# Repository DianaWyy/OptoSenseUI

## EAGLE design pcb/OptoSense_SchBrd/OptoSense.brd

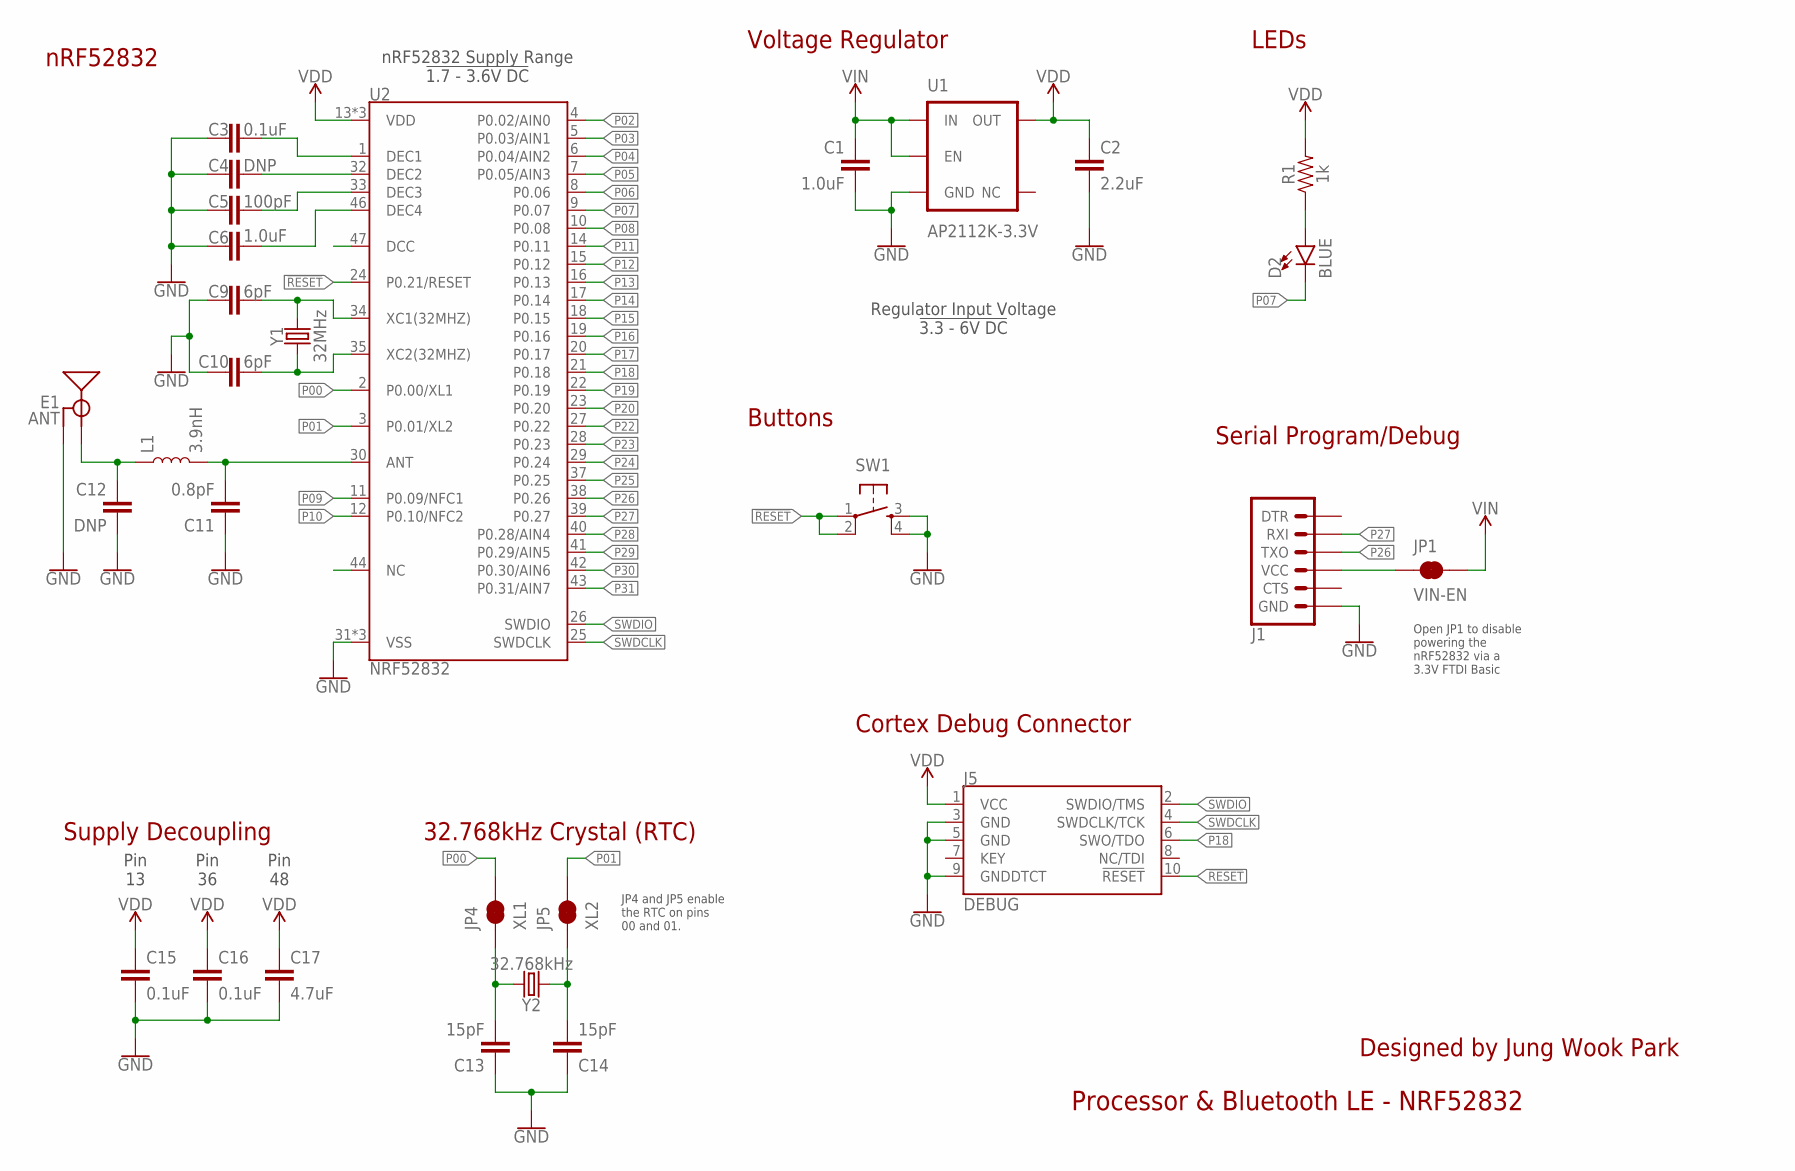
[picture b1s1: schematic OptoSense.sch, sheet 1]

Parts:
C1: 1.0uF; 0603
C2: 2.2uF; 0603
C3, C15, C16: 0.1uF; 0402
C4, C12: DNP; 0402
C5: 100pF; 0402
C6: 1.0uF; 0402
C9, C10: 6pF; 0402
C11: 0.8pF; 0402
C13, C14: 15pF; 0402
C17: 4.7uF; 0603
D2: BLUE; LED-0603
E1: ANT; TRACE_ANTENNA_2.4GHZ_15.2MM
J1: ARDUINO_SERIAL_PROGRAMPTH; 1X06
J5: DEBUG; 2X5-PTH-1.27MM
JP1: VIN-EN; SMT-JUMPER_2_NC_TRACE_SILK
JP4: XL1; PAD-JUMPER-2-NC_BY_TRACE_YES_SILK
JP5: XL2; PAD-JUMPER-2-NC_BY_TRACE_YES_SILK
L1: 3.9nH; 0402
R1: 1k; 0603
SW1: SWITCH_SPST_4_PINRECT; TACTILE_SWITCH_SMD_4.6X2.8MM
U1: AP2112K-3.3V; SOT23-5
U2: NRF52832; QFN48-6X6MM
Y1: 32MHz; CRYSTAL-SMD-2.0X1.6MM
Y2: 32.768kHz; CRYSTAL-SMD-3.2X1.5MM

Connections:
!RESET!: J5.10 (!RESET), SW1.1, SW1.2, U2.24 (P0.21/RESET)
ANT: C11.2, L1.2, U2.30 (ANT)
DCC: U2.47 (DCC)
DEC1: C3.2, U2.1 (DEC1)
DEC2: C4.2, U2.32 (DEC2)
DEC3: C5.2, U2.33 (DEC3)
DEC4: C6.2, U2.46 (DEC4)
GND: C1.2, C2.2, C3.1, C4.1, C5.1, C6.1, C9.1, C10.2, C11.1, C12.2, C13.1, C14.1, C15.2, C16.2, C17.2, E1.GND, J1.6 (GND), J5.3 (GND), J5.5 (GND), J5.9 (GNDDTCT), SW1.3, SW1.4, U1.2 (GND), U2.31 (VSS), U2.45 (VSS), U2.EP (VSS); also elsewhere on the board
unnamed: C13.2, JP4.1, Y2.P$2 (2)
unnamed: C14.2, JP5.1, Y2.P$1 (1)
unnamed: C12.1, E1.ANT (SIGNAL), L1.1
unnamed: J1.4 (VCC), JP1.1
unnamed: D2.A, R1.1
NC: U2.44 (NC)
P00: JP4.2, U2.2 (P0.00/XL1)
P01: JP5.2, U2.3 (P0.01/XL2)
P02: U2.4 (P0.02/AIN0); also elsewhere on the board
P03: U2.5 (P0.03/AIN1); also elsewhere on the board
P04: U2.6 (P0.04/AIN2); also elsewhere on the board
P05: U2.7 (P0.05/AIN3); also elsewhere on the board
P06: U2.8 (P0.06)
P07: D2.C, U2.9 (P0.07)
P08: U2.10 (P0.08)
P09: U2.11 (P0.09/NFC1)
P10: U2.12 (P0.10/NFC2)
P11: U2.14 (P0.11)
P12: U2.15 (P0.12)
P13: U2.16 (P0.13)
P14: U2.17 (P0.14)
P15: U2.18 (P0.15)
P16: U2.19 (P0.16)
P17: U2.20 (P0.17)
P18: J5.6 (SWO/TDO), U2.21 (P0.18)
P19: U2.22 (P0.19)
P20: U2.23 (P0.20)
P22: U2.27 (P0.22); also elsewhere on the board
P23: U2.28 (P0.23); also elsewhere on the board
P24: U2.29 (P0.24); also elsewhere on the board
P25: U2.37 (P0.25); also elsewhere on the board
P26: J1.3 (TXO), U2.38 (P0.26)
P27: J1.2 (RXI), U2.39 (P0.27)
P28: U2.40 (P0.28/AIN4); also elsewhere on the board
P29: U2.41 (P0.29/AIN5); also elsewhere on the board
P30: U2.42 (P0.30/AIN6); also elsewhere on the board
P31: U2.43 (P0.31/AIN7); also elsewhere on the board
SWDCLK: J5.4 (SWDCLK/TCK), U2.25 (SWDCLK)
SWDIO: J5.2 (SWDIO/TMS), U2.26 (SWDIO)
VDD: C2.1, C15.1, C16.1, C17.1, J5.1 (VCC), R1.2, U1.5 (OUT), U2.13 (VDD), U2.36 (VDD), U2.48 (VDD); also elsewhere on the board
VIN: C1.1, JP1.2, U1.1 (IN), U1.3 (EN); also elsewhere on the board
XC1: C9.2, U2.34 (XC1(32MHZ)), Y1.3 (2)
XC2: C10.1, U2.35 (XC2(32MHZ)), Y1.1

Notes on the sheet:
Pin 13
Pin 36
Pin 48
Voltage Regulator
Buttons
LEDs
nRF52832
32.768kHz Crystal (RTC)
Supply Decoupling
Cortex Debug Connector
Serial Program/Debug
Open JP1 to disable powering the nRF52832 via a 3.3V FTDI Basic
JP4 and JP5 enable the RTC on pins 00 and 01.
Regulator Input Voltage !3.3 - 6V DC!
nRF52832 Supply Range !1.7 - 3.6V DC!
Processor & Bluetooth LE - NRF52832
Designed by Jung Wook Park

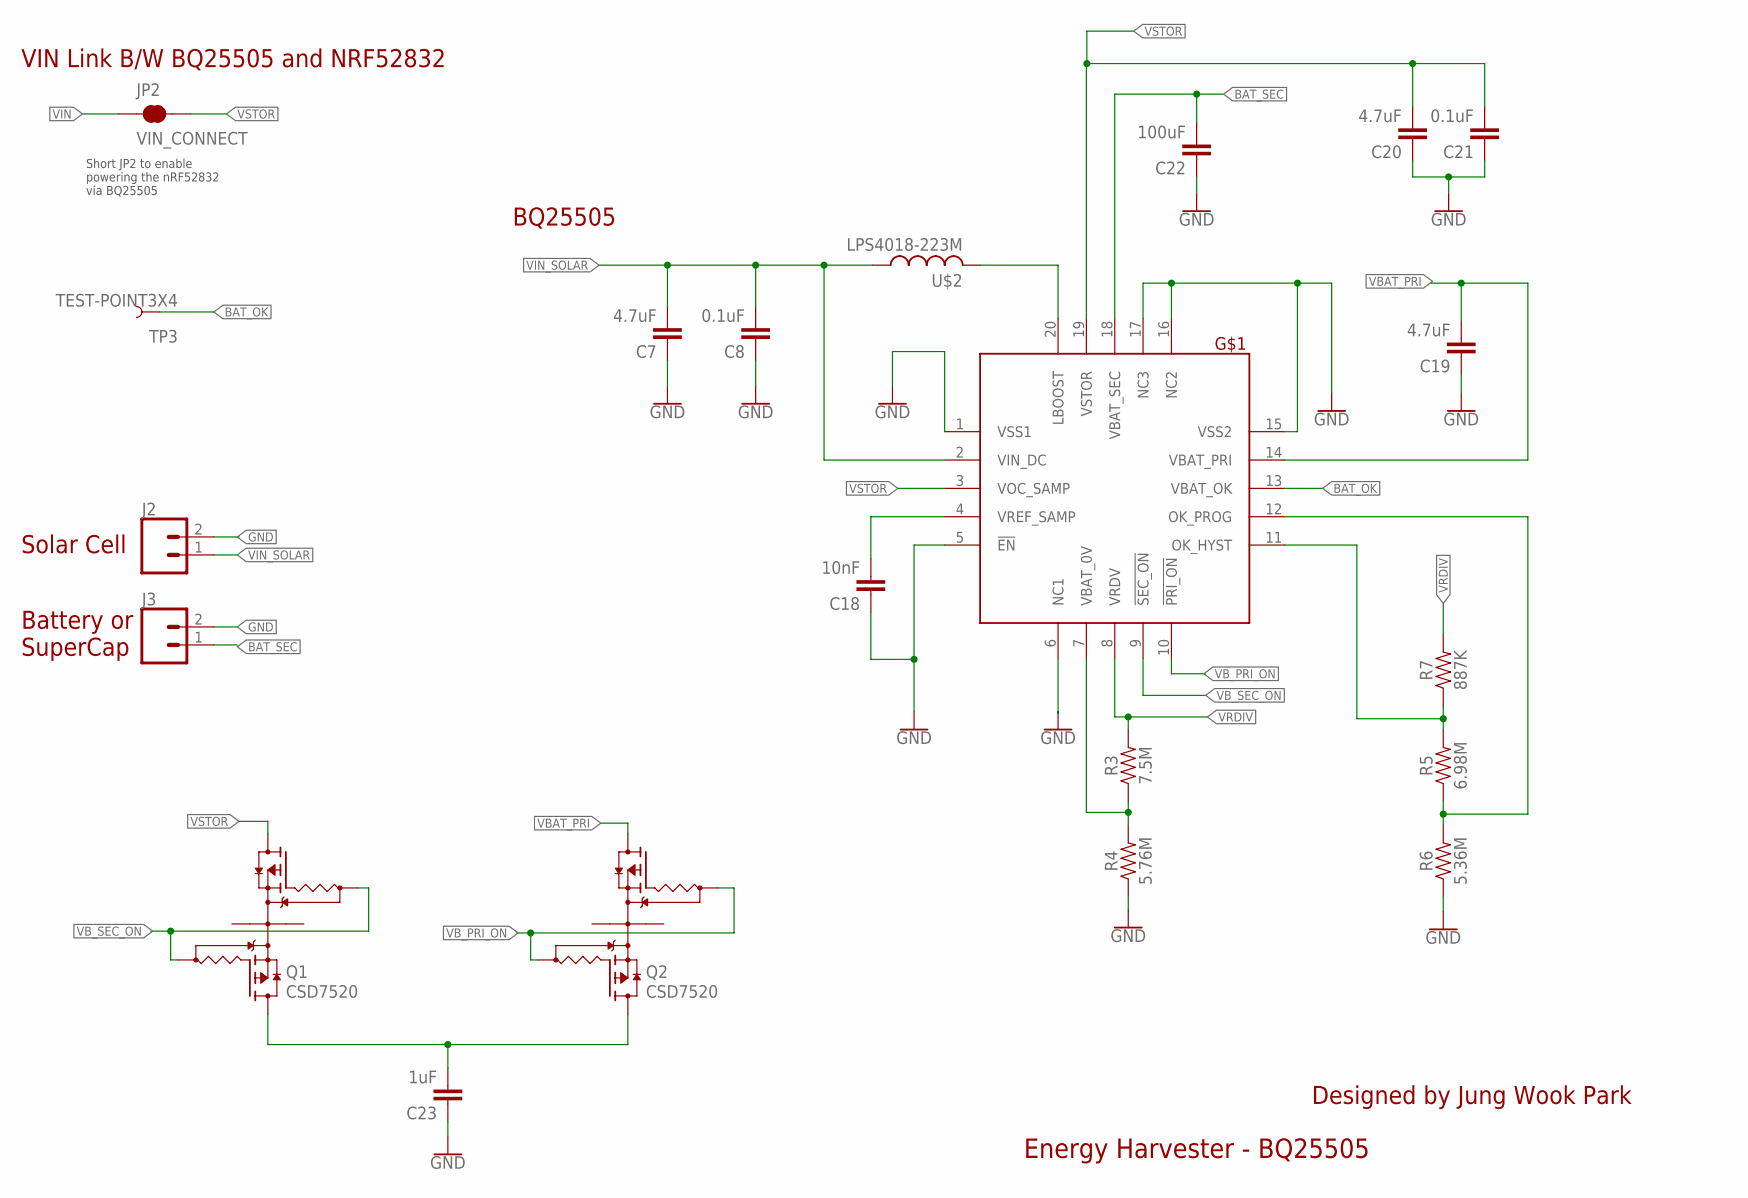
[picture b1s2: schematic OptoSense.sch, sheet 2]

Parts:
C7, C19, C20: 4.7uF; 0402
C8, C21: 0.1uF; 0402
C18: 10nF; 0402
C22: 100uF; 0402
C23: 1uF; 0402
J2, J3: CONN_02; 1X02
JP2: VIN_CONNECT; SMT-JUMPER_2_NC_TRACE_SILK
Q1, Q2: CSD7520; CSD75205W1015
R3: 7.5M; 0603
R4: 5.76M; 0603
R5: 6.98M; 0603
R6: 5.36M; 0603
R7: 887K; 0603
TP3: TEST-POINT3X4; PAD.03X.04
U$1: BQ25505; QFN20
U$2: LPS4018-223M; LPS4018

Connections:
BAT_OK: TP3.P$1, U$1.13 (VBAT_OK)
BAT_SEC: C22.2, J3.1, U$1.18 (VBAT_SEC)
GND: C7.1, C8.1, C18.1, C19.1, C20.1, C21.1, C22.1, C23.1, J2.2, J3.2, R4.1, R6.1, U$1.1 (VSS1), U$1.5 (!EN), U$1.6 (NC1), U$1.15 (VSS2), U$1.16 (NC2), U$1.17 (NC3); also elsewhere on the board
unnamed: U$1.20 (LBOOST), U$2.P$2 (2)
unnamed: C18.2, U$1.4 (VREF_SAMP)
unnamed: R3.1, R4.2, U$1.7 (VBAT_0V)
unnamed: R5.1, R6.2, U$1.12 (OK_PROG)
unnamed: R5.2, R7.1, U$1.11 (OK_HYST)
unnamed: C23.2, Q1.D1, Q2.D1
VBAT_PRI: C19.2, Q2.D2, U$1.14 (VBAT_PRI)
VB_PRI_ON: Q2.G1, Q2.G2, U$1.10 (!PRI_ON)
VB_SEC_ON: Q1.G1, Q1.G2, U$1.9 (!SEC_ON)
VIN: JP2.1; also elsewhere on the board
VIN_SOLAR: C7.2, C8.2, J2.1, U$1.2 (VIN_DC), U$2.P$1 (1)
VRDIV: R3.2, R7.2, U$1.8 (VRDV)
VSTOR: C20.2, C21.2, JP2.2, Q1.D2, U$1.3 (VOC_SAMP), U$1.19 (VSTOR)

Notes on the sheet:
Energy Harvester - BQ25505
BQ25505
Solar Cell
Battery or SuperCap
Short JP2 to enable powering the nRF52832 via BQ25505
VIN Link B/W BQ25505 and NRF52832
Designed by Jung Wook Park

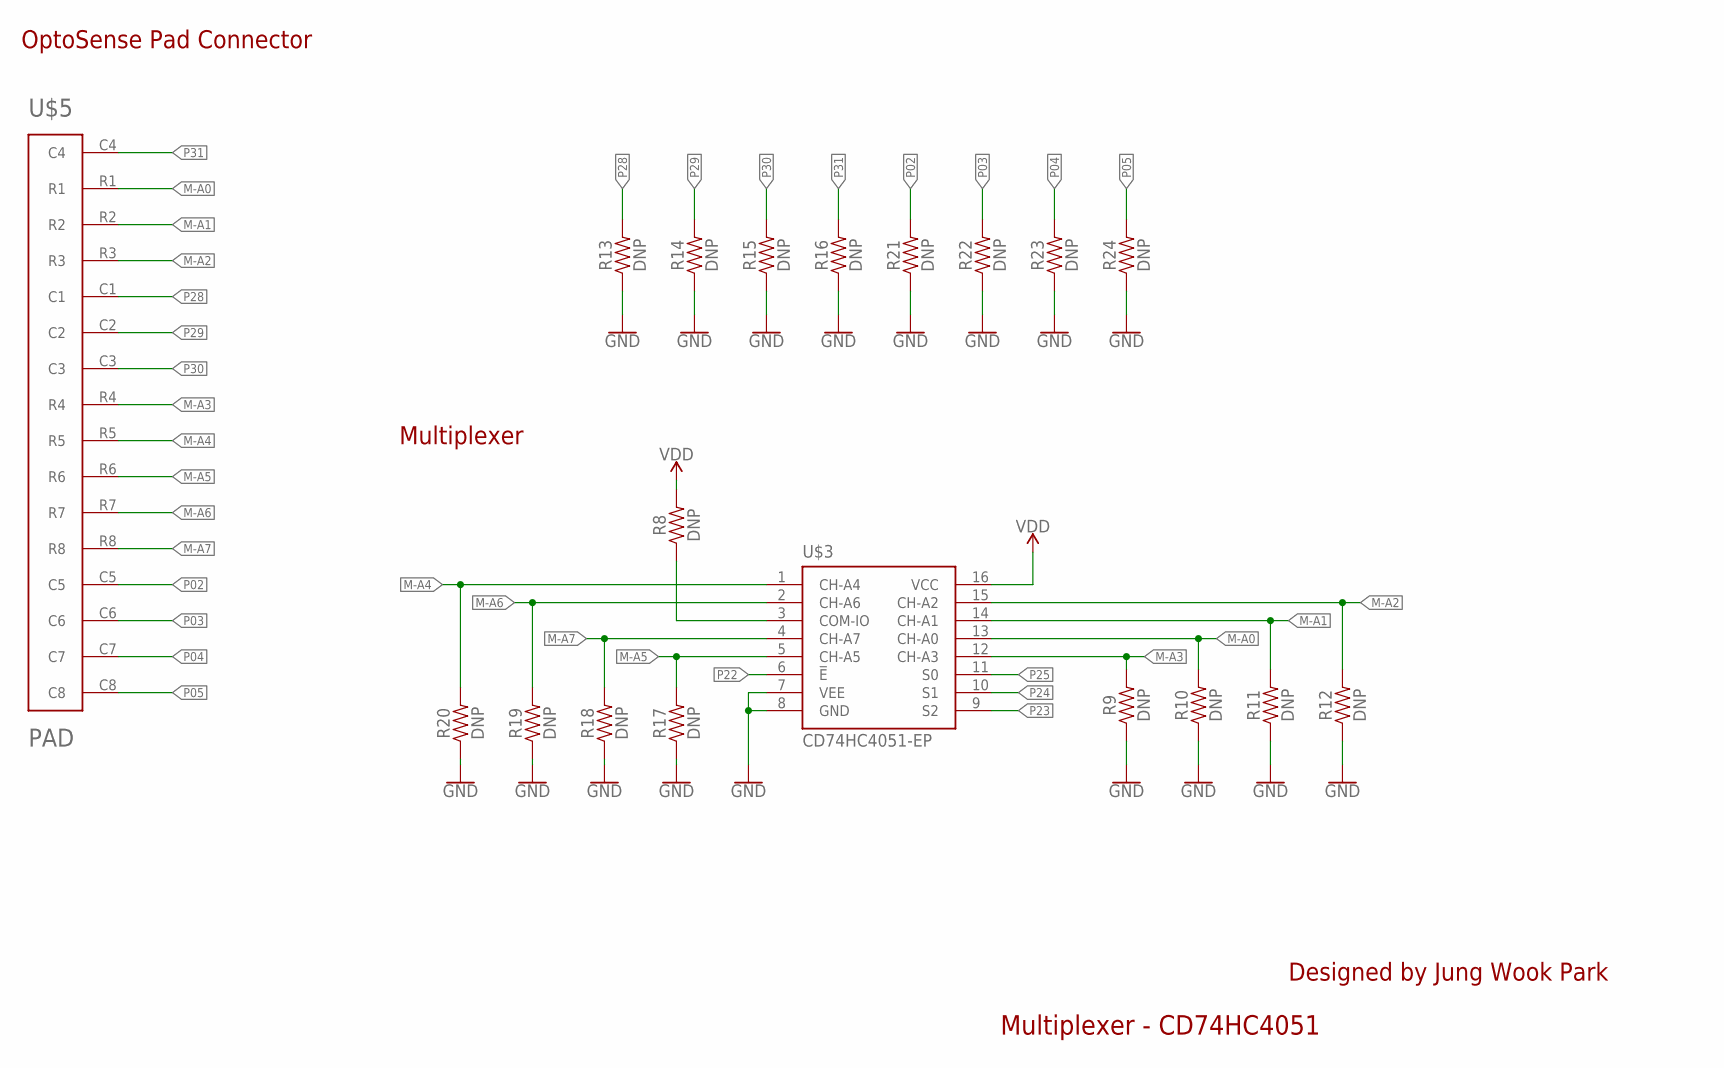
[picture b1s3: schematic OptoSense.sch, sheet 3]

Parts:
R8, R9, R10, R11, R12, R13, R14, R15, R16, R17, R18, R19, R20, R21, R22, R23, R24: DNP; 0603
U$3: CD74HC4051-EP; SO16
U$5: PAD; PADS-16

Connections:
GND: R9.1, R10.1, R11.1, R12.1, R13.1, R14.1, R15.1, R16.1, R17.1, R18.1, R19.1, R20.1, R21.1, R22.1, R23.1, R24.1, U$3.7 (VEE), U$3.8 (GND); also elsewhere on the board
M-A0: R10.2, U$3.13 (CH-A0), U$5.R1
M-A1: R11.2, U$3.14 (CH-A1), U$5.R2
M-A2: R12.2, U$3.15 (CH-A2), U$5.R3
M-A3: R9.2, U$3.12 (CH-A3), U$5.R4
M-A4: R20.2, U$3.1 (CH-A4), U$5.R5
M-A5: R17.2, U$3.5 (CH-A5), U$5.R6
M-A6: R19.2, U$3.2 (CH-A6), U$5.R7
M-A7: R18.2, U$3.4 (CH-A7), U$5.R8
unnamed: R8.1, U$3.3 (COM-IO)
P02: R21.2, U$5.C5; also elsewhere on the board
P03: R22.2, U$5.C6; also elsewhere on the board
P04: R23.2, U$5.C7; also elsewhere on the board
P05: R24.2, U$5.C8; also elsewhere on the board
P22: U$3.6 (!E); also elsewhere on the board
P23: U$3.9 (S2); also elsewhere on the board
P24: U$3.10 (S1); also elsewhere on the board
P25: U$3.11 (S0); also elsewhere on the board
P28: R13.2, U$5.C1; also elsewhere on the board
P29: R14.2, U$5.C2; also elsewhere on the board
P30: R15.2, U$5.C3; also elsewhere on the board
P31: R16.2, U$5.C4; also elsewhere on the board
VDD: R8.2, U$3.16 (VCC); also elsewhere on the board

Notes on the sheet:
Designed by Jung Wook Park
Multiplexer - CD74HC4051
Multiplexer
OptoSense Pad Connector

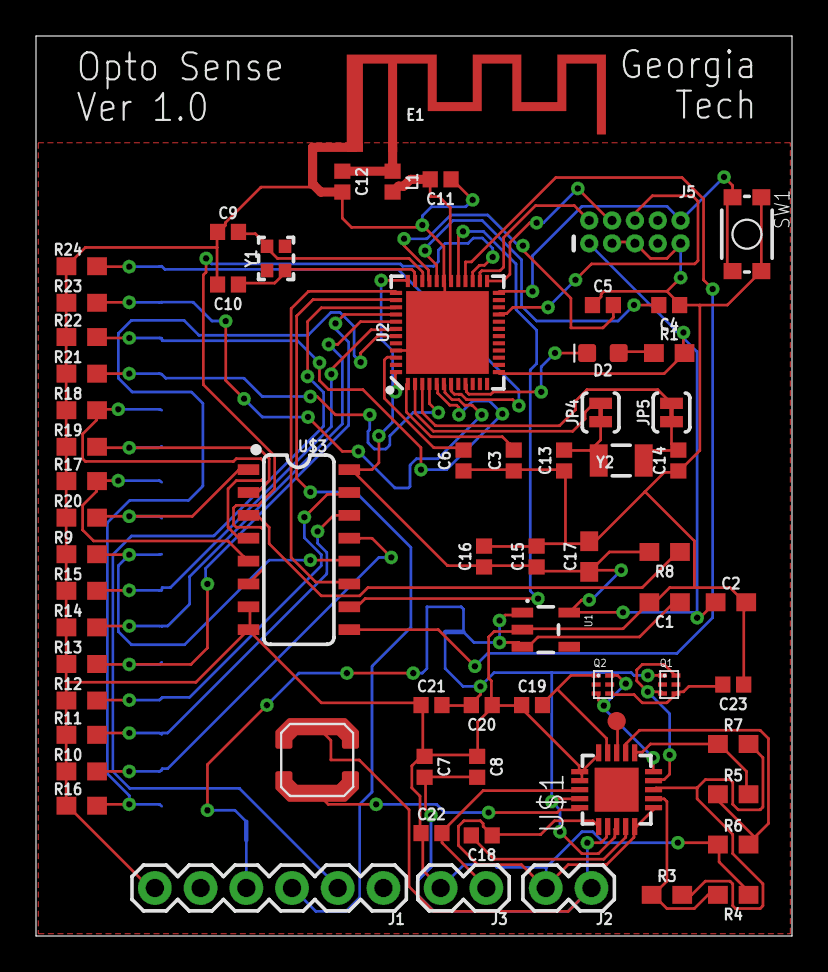
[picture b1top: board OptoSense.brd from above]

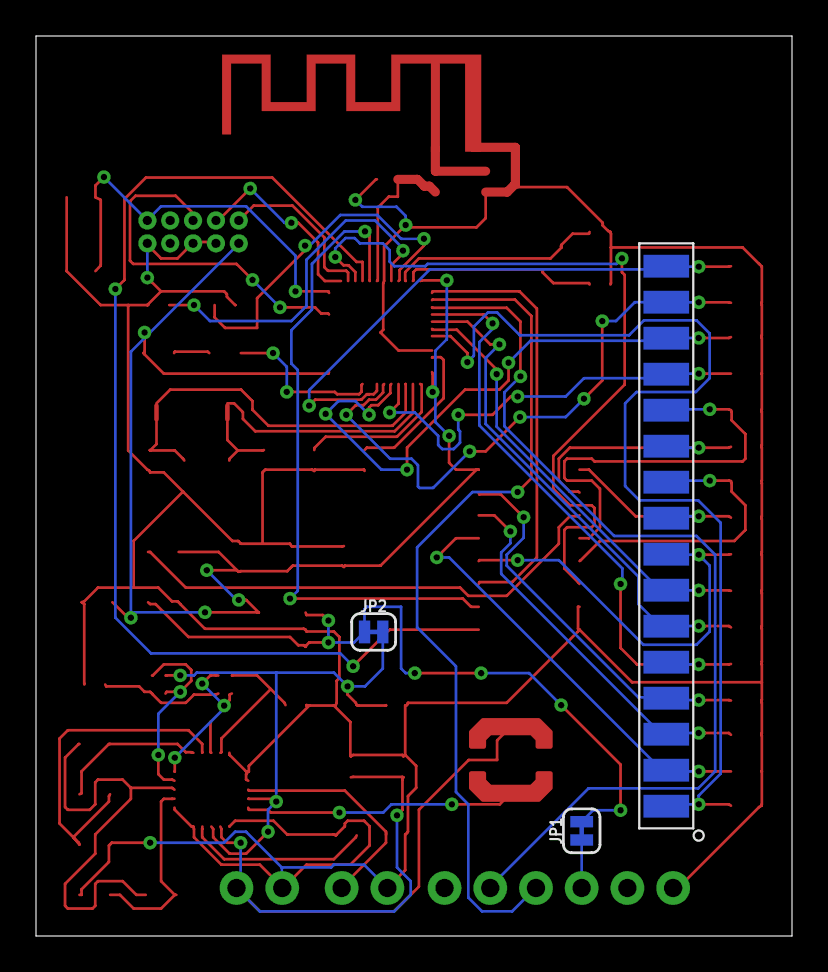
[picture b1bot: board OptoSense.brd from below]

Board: 2 copper layers, 42.0 x 50.0 mm, 69 parts (3 on the bottom side), 59 nets.

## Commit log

2021-10-31 Upload UI implementations
2021-10-31 Add supporting files

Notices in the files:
parts and their libraries:
SparkFun-Capacitors: Licensing: Creative Commons ShareAlike 4.0 International - https://creativecommons.org/licenses/by-sa/4.0
